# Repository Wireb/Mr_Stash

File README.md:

# Mr Stash
Mr Stash was a badge I built for DC26 to use for trade of other badges and SAOs. 
License is MIT so do what you want with it just don't litigate me. 

**NOTE** I screwed up and wipped my laptop hard drive before pulling the final firmware version off it. The version in this repo is from right before I left for DC26 and is missing the following items:
- LED mode that cycles though all patterns
- Bonus hidden Morse code message at high pattern offset 
- All but one vibe pattern
- Vibe mode that cycles though all patterns once
- Updated touch sensor code. Code in repo works good in my house in MN but was unusable in the dry Nevada environment. 

## InkScape
Inkscape was used for the "art" layout of the badge. This mainly consisted of the outline, Stash, motors, IR sensor locations, and eyebrows. These layers were converted into SVG files then imported into KiCad as footprints. 
The edge cuts were post processed via Perl scripts to convert it from a filled zone (KiCad 3D viewer pukes on this) to line segments. 

## KiCad
This is a KiCad 4.x project that has been updated to 5.0 so some things are a little funky. 
Note the following parts were not populated in the final design: 1x 0.1uF cap, 4x 22uF cap, 2x diodes, 1x badge bus connector, 1x SAO connector 

## mplabX
This is a mplabX 4.2 project that was upgraded mid project to 5.0. All programming / debug was done with a PicKit4 or a PicKit3 (killed my PK4 just before leaving for DC26)
The firmware source is all contained in Mr_Stash.asm (see note above about missing functions)

## documentation
This is a XLS/PDF dump of the spreadsheet documentation I was using during development. 
All the menu items and command protocol are detailed in here. 

Copyright (c) 2018 Peter Shabino

Permission is hereby granted, free of charge, to any person obtaining a copy of this hardware, software, and associated documentation files 
(the "Product"), to deal in the Product without restriction, including without limitation the rights to use, copy, modify, merge, publish, 
distribute, sublicense, and/or sell copies of the Product, and to permit persons to whom the Product is furnished to do so, subject to the 
following conditions:

The above copyright notice and this permission notice shall be included in all copies or substantial portions of the Product.

THE PRODUCT IS PROVIDED "AS IS", WITHOUT WARRANTY OF ANY KIND, EXPRESS OR IMPLIED, INCLUDING BUT NOT LIMITED TO THE WARRANTIES OF 
MERCHANTABILITY, FITNESS FOR A PARTICULAR PURPOSE AND NONINFRINGEMENT. IN NO EVENT SHALL THE AUTHORS OR COPYRIGHT HOLDERS BE LIABLE 
FOR ANY CLAIM, DAMAGES OR OTHER LIABILITY, WHETHER IN AN ACTION OF CONTRACT, TORT OR OTHERWISE, ARISING FROM, OUT OF OR IN CONNECTION 
WITH THE PRODUCT OR THE USE OR OTHER DEALINGS IN THE PRODUCT.

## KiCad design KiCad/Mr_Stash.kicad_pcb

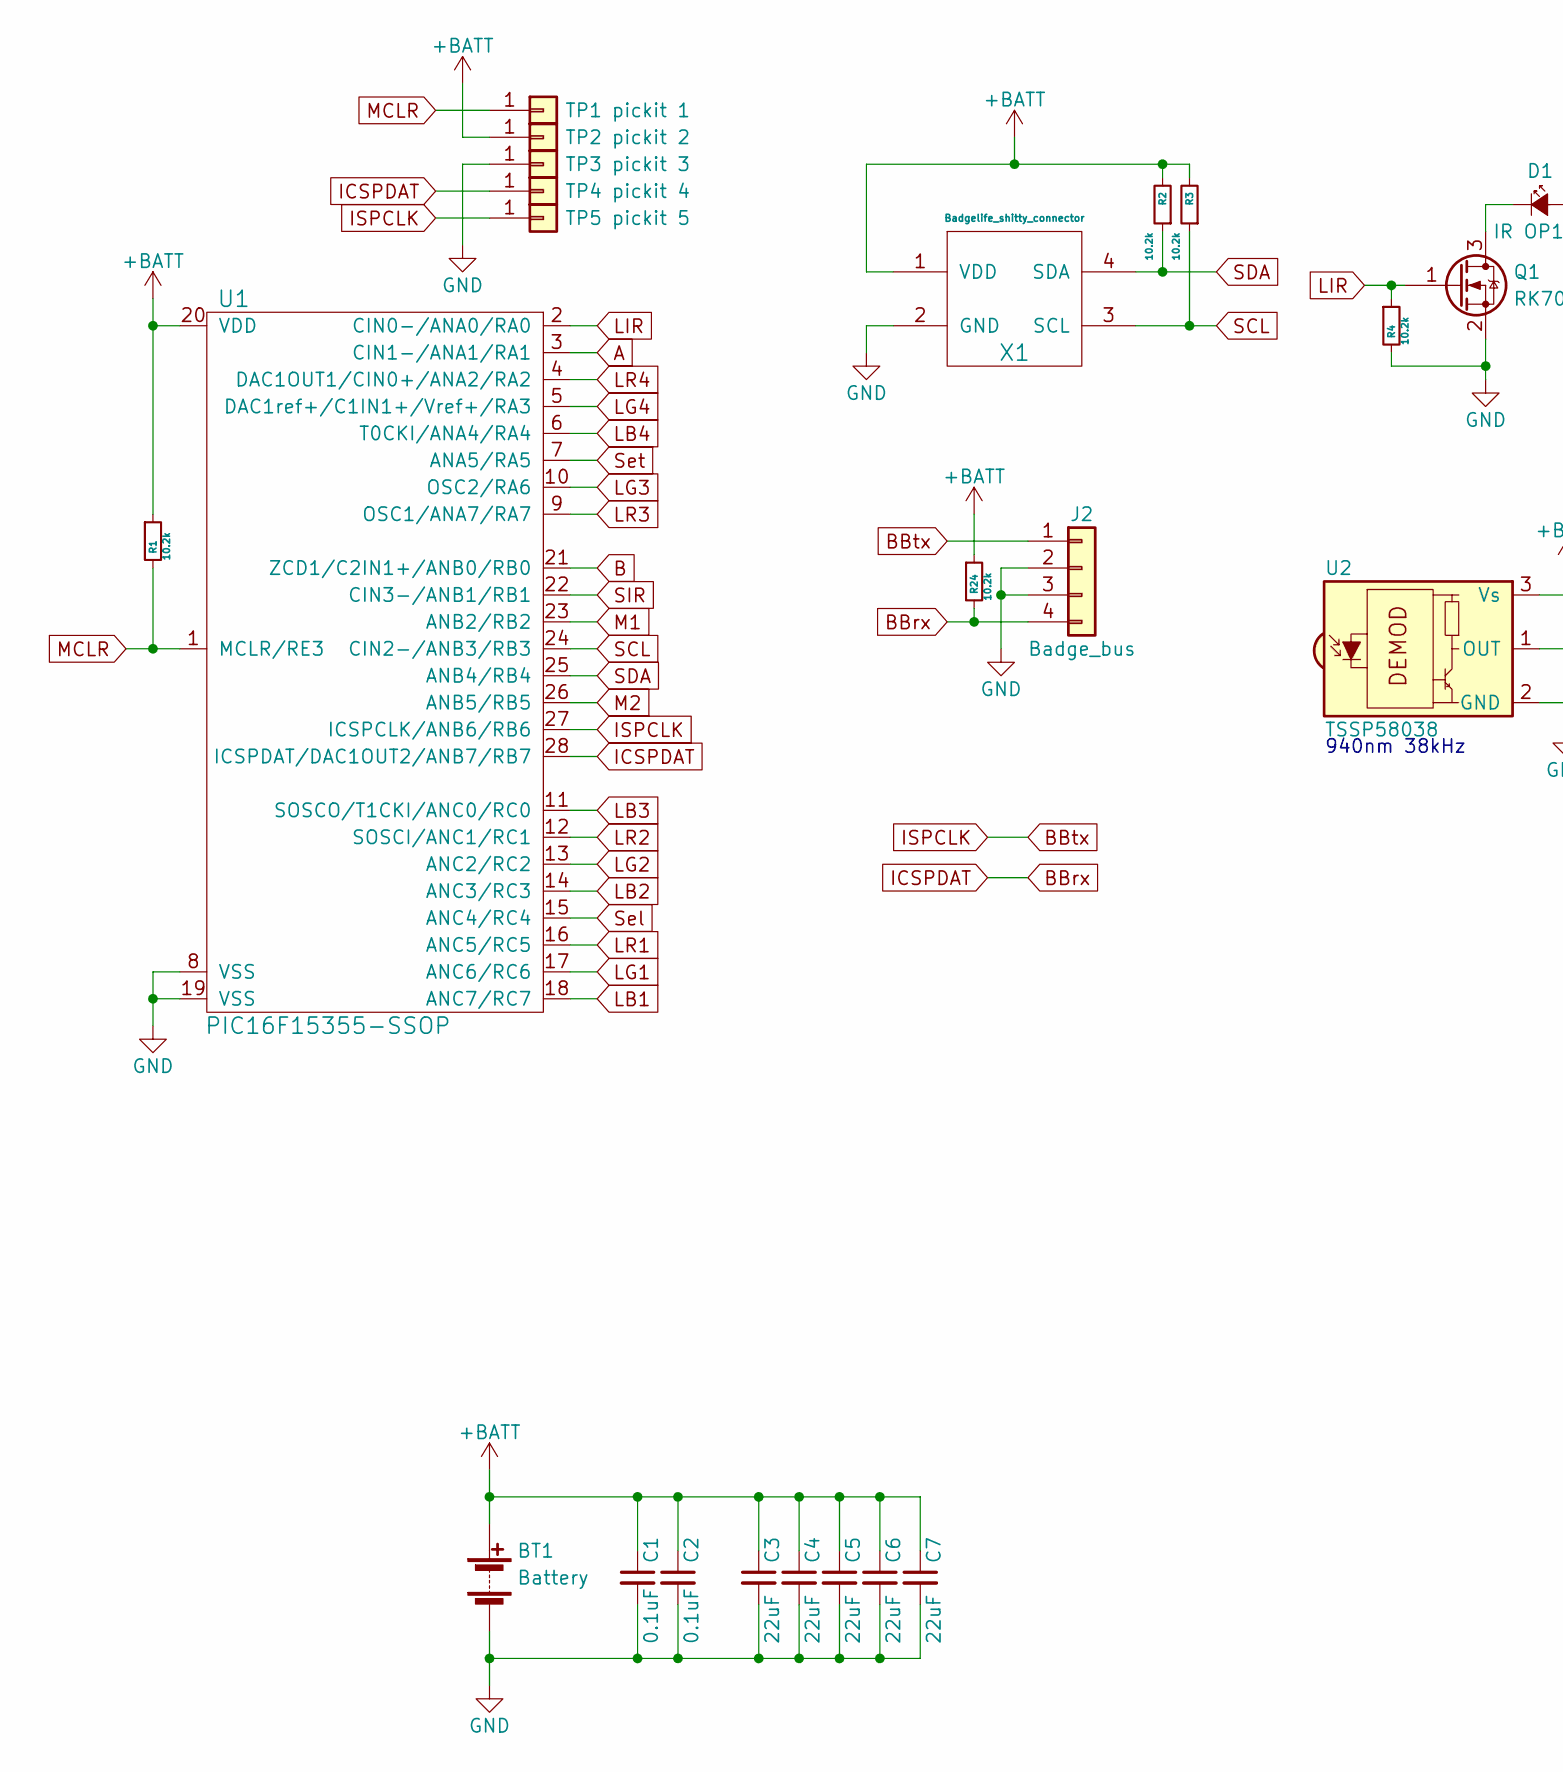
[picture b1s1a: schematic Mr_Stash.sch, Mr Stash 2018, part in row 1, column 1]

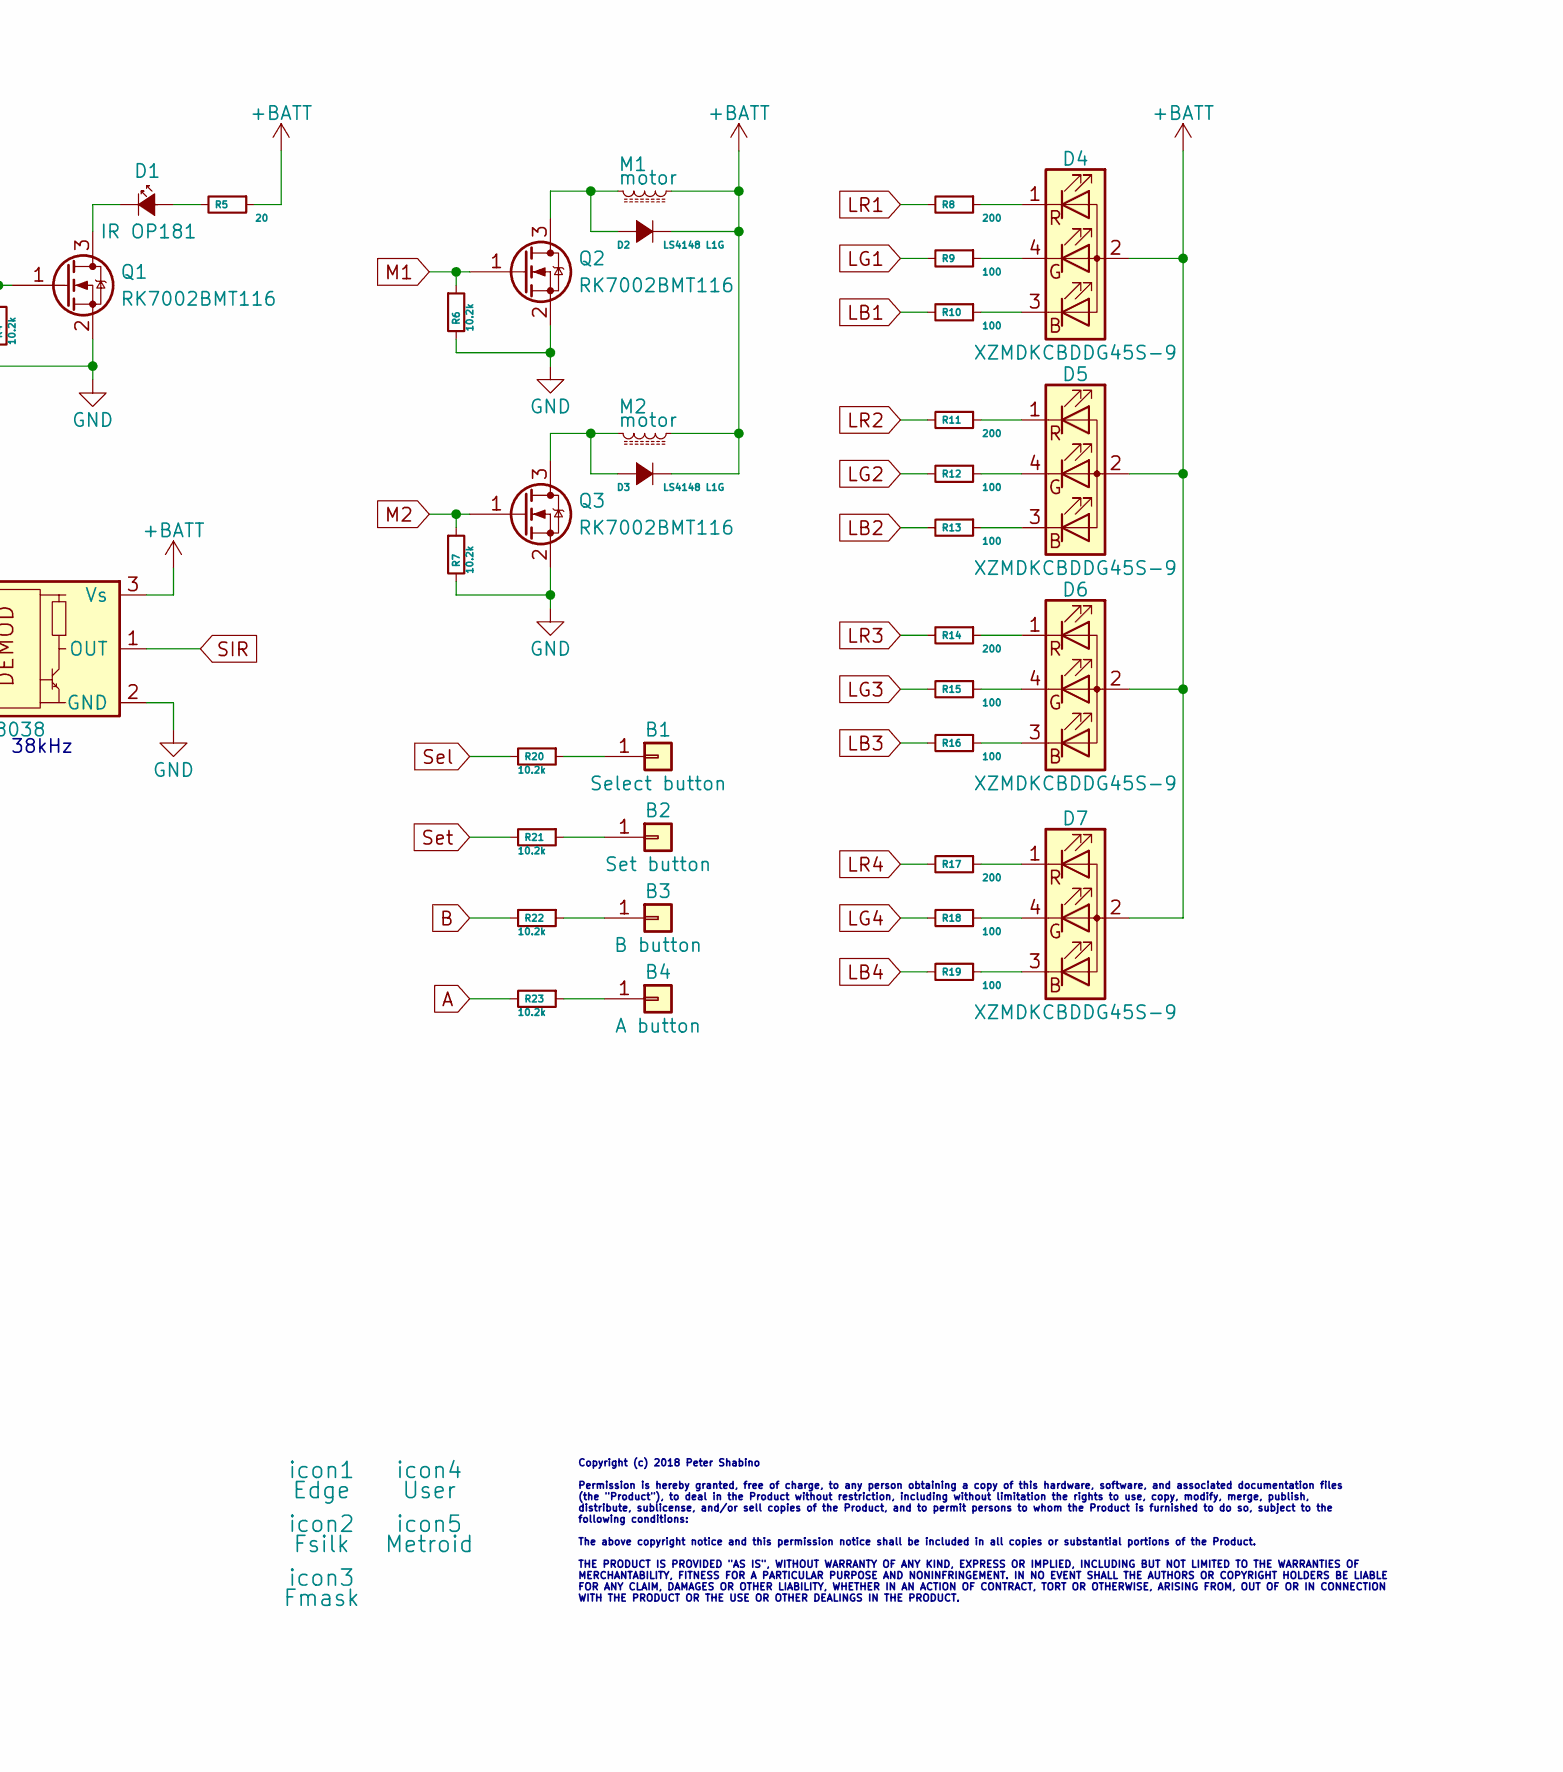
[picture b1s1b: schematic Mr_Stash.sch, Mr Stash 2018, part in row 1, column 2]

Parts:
B1: Select button; blank_button_7.5mm
B2: Set button; blank_button_7.5mm
B3: A button; blank_button_7.5mm
B4: B button; blank_button_7.5mm
BT1: Battery; Keystone_3_AA_battery_holder
C1, C2: 0.1uF; C_0805
C3, C4, C5, C6, C7: 22uF; C_0805
D1: IR OP181; OP181_TT_electronics_IR
D2, D3: LS4148 L1G; SOD-80V-LS34
D4, D5, D6, D7: XZMDKCBDDG45S-9; XZMDKCBDDG45S-9-3mm-hole
J2: Badge_bus; 10120045-40-LF
M1, M2: motor; Pager_motor_10mm_smt
Q1, Q2, Q3: RK7002BMT116; SOT-23
R1, R2, R3, R4, R6, R7, R20, R21, R22, R23, R24: 10.2k; R_0603
R5: 20; R_1206
R8, R11, R14, R17: 200; R_0603
R9, R10, R12, R13, R15, R16, R18, R19: 100; R_0603
TP1: pickit 1; 80mill_sqr_test_point
TP2: pickit 2; 80mill_test_point
TP3: pickit 3; 80mill_test_point
TP4: pickit 4; 80mill_test_point
TP5: pickit 5; 80mill_test_point
U1: PIC16F15355-SSOP; SSOP-28_5.3x10.2mm_Pitch0.65mm
U2: TSSP58038; TSSP58038_custom_45_SMT
X1: Badgelife_shitty_connector; Badgelife-Shitty-2x2
icon1: Edge; mr-stash_cuts
icon2: Fsilk; mr-stash_silk
icon3: Fmask; mr-stash_fmask
icon4: User; mr-stash_user
icon5: Metroid; metroid

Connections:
+BATT: BT1.1 (+), C1.1, C2.1, C3.1, C4.1, C5.1, C6.1, C7.1, D2.1 (K), D3.1 (K), D4.2 (A), D5.2 (A), D6.2 (A), D7.2 (A), M1.1, M2.1, R1.1, R2.2, R3.2, R5.1, R24.1, TP2.1, U1.20 (VDD), U2.3 (Vs), X1.1 (VDD)
A: R22.2, U1.21 (ZCD1/C2IN1+/ANB0/RB0)
B: R23.2, U1.3 (CIN1-/ANA1/RA1)
BBrx: J2.4, R24.2, TP4.1, U1.28 (ICSPDAT/DAC1OUT2/ANB7/RB7)
BBtx: J2.1, TP5.1, U1.27 (ICSPCLK/ANB6/RB6)
GND: BT1.2 (-), C1.2, C2.2, C3.2, C4.2, C5.2, C6.2, C7.2, J2.2, J2.3, Q1.2 (S), Q2.2 (S), Q3.2 (S), R4.2, R6.2, R7.2, TP3.1, U1.8 (VSS), U1.19 (VSS), U2.2 (GND), X1.2 (GND)
LB1: R10.2, U1.18 (ANC7/RC7)
LB2: R13.2, U1.14 (ANC3/RC3)
LB3: R16.2, U1.11 (SOSCO/T1CKI/ANC0/RC0)
LB4: R19.2, U1.6 (T0CKI/ANA4/RA4)
LG1: R9.2, U1.17 (ANC6/RC6)
LG2: R12.2, U1.13 (ANC2/RC2)
LG3: R15.2, U1.10 (OSC2/RA6)
LG4: R18.2, U1.5 (DAC1ref+/C1IN1+/Vref+/RA3)
LIR: Q1.1 (G), R4.1, U1.2 (CIN0-/ANA0/RA0)
LR1: R8.2, U1.16 (ANC5/RC5)
LR2: R11.2, U1.12 (SOSCI/ANC1/RC1)
LR3: R14.2, U1.9 (OSC1/ANA7/RA7)
LR4: R17.2, U1.4 (DAC1OUT1/CIN0+/ANA2/RA2)
M1: Q2.1 (G), R6.1, U1.23 (ANB2/RB2)
M2: Q3.1 (G), R7.1, U1.26 (ANB5/RB5)
MCLR: R1.2, TP1.1, U1.1 (MCLR/RE3)
unnamed: B1.1, R20.1
unnamed: B2.1, R21.1
unnamed: B3.1, R22.1
unnamed: B4.1, R23.1
unnamed: D1.1 (K), Q1.3 (D)
unnamed: D1.2 (A), R5.2
unnamed: D2.2 (A), M1.2, Q2.3 (D)
unnamed: D3.2 (A), M2.2, Q3.3 (D)
unnamed: D4.1 (RK), R8.1
unnamed: D4.3 (BK), R10.1
unnamed: D4.4 (GK), R9.1
unnamed: D5.1 (RK), R11.1
unnamed: D5.3 (BK), R13.1
unnamed: D5.4 (GK), R12.1
unnamed: D6.1 (RK), R14.1
unnamed: D6.3 (BK), R16.1
unnamed: D6.4 (GK), R15.1
unnamed: D7.1 (RK), R17.1
unnamed: D7.3 (BK), R19.1
unnamed: D7.4 (GK), R18.1
SCL: R3.1, U1.24 (CIN2-/ANB3/RB3), X1.3 (SCL)
SDA: R2.1, U1.25 (ANB4/RB4), X1.4 (SDA)
SIR: U1.22 (CIN3-/ANB1/RB1), U2.1 (OUT)
Sel: R20.2, U1.15 (ANC4/RC4)
Set: R21.2, U1.7 (ANA5/RA5)

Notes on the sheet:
940nm 38kHz
Copyright (c) 2018 Peter Shabino Permission is hereby granted, free of charge, to any person obtaining a copy of this hardware, software, and associated documentation files (the "Product"), to deal in the Product without restriction, including without limitation the rights to use, copy, modify, mer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

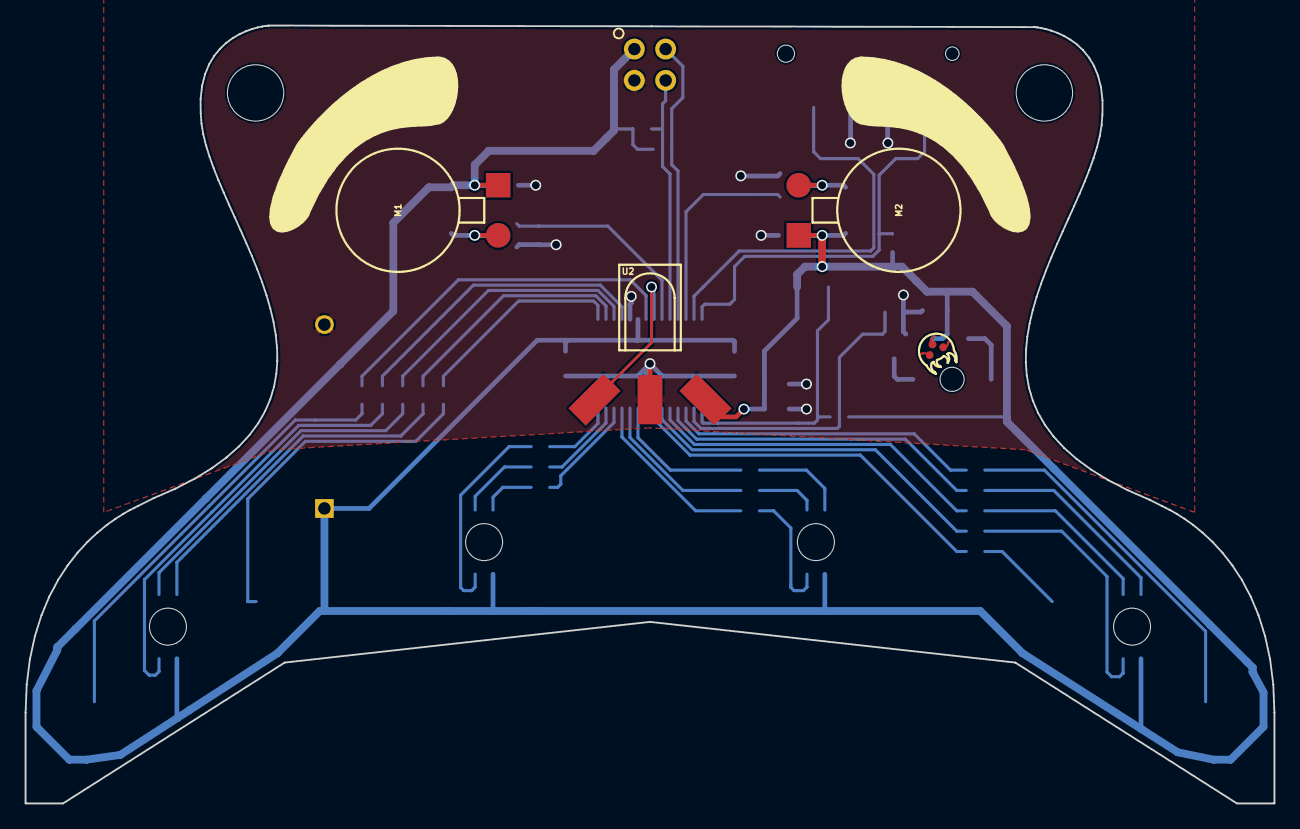
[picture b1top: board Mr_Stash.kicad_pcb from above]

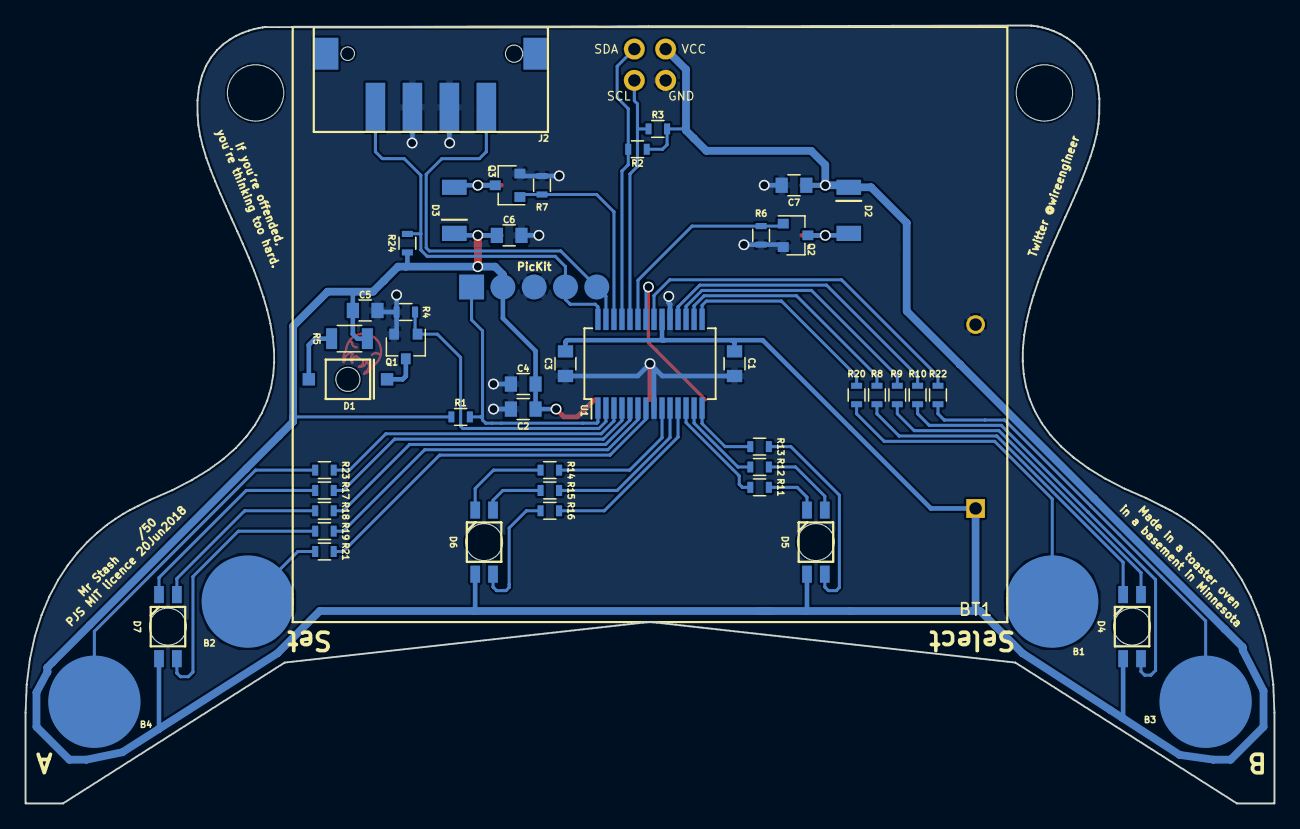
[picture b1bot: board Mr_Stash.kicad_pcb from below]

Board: 2 copper layers, 101.3 x 63.1 mm, 62 parts (53 on the bottom side), 47 nets.

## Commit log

2018-08-19 :octocat: Added .gitattributes & .gitignore files
2018-08-19 First publish
    Pushing design up
2018-08-19 spelling update
2018-08-19 formatting

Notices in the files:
KiCad/Mr_Stash.kicad_pcb:
PJS MIT licence 20Jun2018
